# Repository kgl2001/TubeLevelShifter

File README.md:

# Tube Level Shifter for use with BBC Micro and Master 128 computers.

This project allows a Raspberry Pi to be connected to the Tube port on the BBC Micro and Master 128 computers. With the [PiTubeDirect](https://github.com/hoglet67/PiTubeDirect/wiki) software loaded onto the Pi, the following list of co-processors can be emulated:

```
 n   Processor - *FX 151,230,n
 0   65C02 (fast)
 1   65C02 (3MHz)
 2   65C102 (fast)
 3   65C102 (4MHz)
 4   Z80 (1.21)
 5   Z80 (2.00)
 6   Z80 (2.2c)
 7   Z80 (2.30)
 8   80186
 9   MC6809
11   PDP-11
12   ARM2
13   32016
14   Disable
15   ARM Native
16   LIB65C02 64K
17   LIB65C02 256K Turbo
18   65C816 (Dossy)
19   65C816 (ReCo)
20   OPC5LS
21   OPC6
22   OPC7
23   RISC-V
24 * 65C02 (JIT)
28   Ferranti F100-L
```

Most Pi models are compatible with PiTubeDirect. The smaller PiZero, PiZeroW or PiZero2W and level shifter can sit under a Beeb or Master.

The larger Pi1, Pi2, Pi3A/B & Pi4 models are also supported via a cable as they won't fit under the computer.

The latest PiTubeDirect software can be downloaded from the following site:

https://github.com/hoglet67/PiTubeDirect/releases

Some general notes:

* The source files are to be used with KiCAD v9.0.0 or later.
* The gerber files have been optimised for fabrication by JLCPCB. In particular, there is a 8mmx8mm silkscreen box on the rear of the PCB. This is to allow a 2D barcode, with unique serial number to be printed on the PCB.
* If you want the barcode to be added, then make sure to select this option in the 'Mark on PCB' field, and make sure to select 'Specify position' in the '2D Barcode Position' field, otherwise you will end up with a white 8mm x 8mm box printed on your PCB and a 8mm x 8mm barcode printed at a position of JLCPCBs choosing. Thrust me on this!
* If you don't want the barcode added, then remove the 8mm x 8mm box from the silkscreen layer and regenerate the gerbers. Otherwise you will end up with a white 8mm x 8mm box printed on your PCB.
* A combined CPL / BOM file is included in the gerber directory. Again, this is for use with JLCPCB, if you want to use their PCBA (PCB Assembly) to solder on all the SMD parts.
* You will need to source suitable 40 pin right angle and 40 pin straight through sockets, and solder these onto the PCB. The Raspberry Pi will connect to the 40 pin straight through socket and the level shifter will plug into the tube port via the 40 pin right angle socket.
* Be aware that it is possible to misalign the 40 pin right angle socket both vertically and horizontally when plugging it into the tube port so take care to ensure it is aligned correctly.
* The pins on the tube port connector may be tarnished if the header has not been used for many years. This can cause unreliable operation. This can usually be fixed with repeated removal and re-insertion of the level shifter into the header.
* Do not use a ribbon cable to connect the Raspberry Pi to the level shifter. Instead, the Raspberry Pi should be plugged directly into the level shifter.
* The level shifter can be plugged directly into the tube port in the well underneath the keyboard, or it can be attached to the tube port via a 40 way male / female ribbon cable.
* There is limited space in the well underneath the Master, so the the level shifter should initially be inserted at an angle and then straightened out as the level shifter is pushed home into the tube port.
* Due to the limited space underneath the Master, a compromise had to be made on the overall size of the level shifter board. Therefore, when fitting the level shifter into the Model B it may not be possible to push the level shifter fully into the tube port socket, otherwise the front face of the Pi will clash with part of the computer case.
* An optional power header can be attached to the level shifter. This header can then be used to power the Pi1MHz level shifter and assocaited Raspberry Pi, if attached to the 1MHz bus. The 5v supply is protected by a 500mA Poylfuse.
* If the level shifter is connected to the tube port via a ribbon cable then the simplest way to power the level shifter and Raspberry Pi is via a standard Raspberry Pi power supply connected to the Raspberry Pi. This will also power the level shifter. In this case, jumper J1 should be removed to prevent the Raspberry Pi supply from powering the main computer.

## Developer

The 1MHz level shifter board is developed and maintained by Ken Lowe.
    
## Hardware License (Creative Commons BY-SA 4.0)

Please see the following link for details: https://creativecommons.org/licenses/by-sa/4.0/

You are free to:

Share - copy and redistribute the material in any medium or format
Adapt - remix, transform, and build upon the material
for any purpose, even commercially.

This license is acceptable for Free Cultural Works.

The licensor cannot revoke these freedoms as long as you follow the license terms.

Under the following terms:

Attribution - You must give appropriate credit, provide a link to the license, and indicate if changes were made. You may do so in any reasonable manner, but not in any way that suggests the licensor endorses you or your use.

ShareAlike - If you remix, transform, or build upon the material, you must distribute your contributions under the same license as the original.

No additional restrictions - You may not apply legal terms or technological measures that legally restrict others from doing anything the license permits.

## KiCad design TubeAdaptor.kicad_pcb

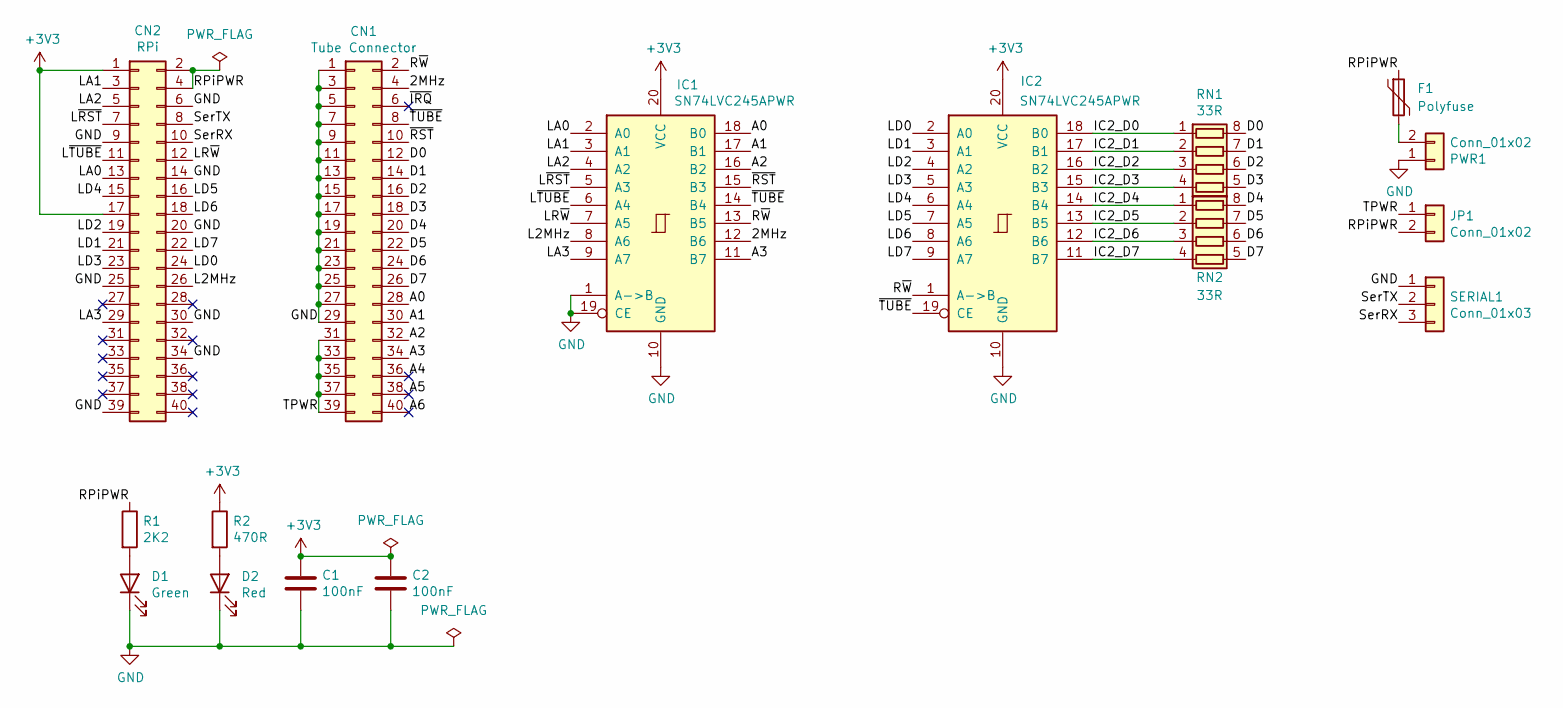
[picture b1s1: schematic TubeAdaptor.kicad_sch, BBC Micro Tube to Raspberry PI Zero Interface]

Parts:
C1, C2: 100nF; C_0402_1005Metric; JLC Part Number C1525
CN1: Tube Connector; PinSocket_2x20_P2.54mm_Horizontal_Reverse
CN2: RPi; PinSocket_2x20_P2.54mm_Vertical
D1: Green; LED_0603_1608Metric; JLC Part Number C72043
D2: Red; LED_0603_1608Metric; JLC Part Number C2286
F1: Polyfuse; Fuse_0603_1608Metric; JLC Part Number C883095
IC1, IC2: SN74LVC245APWR; TSSOP-20_4.4x6.5mm_P0.65mm; JLC Part Number C7848
JP1: Conn_01x02; PinHeader_1x02_P2.54mm_Vertical
PWR1: Conn_01x02; PinHeader_1x02_P2.54mm_Horizontal
R1: 2K2; R_0402_1005Metric; JLC Part Number C25879
R2: 470R; R_0402_1005Metric; JLC Part NumberJLC Part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 C25117
RN1, RN2: 33R; R_Array_Concave_4x0402; JLC Part Number C25501
SERIAL1: Conn_01x03; PinHeader_1x03_P2.54mm_Horizontal

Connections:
+3V3: C1.1, C2.1, CN2.1, CN2.17, IC1.20 (VCC), IC2.20 (VCC), R2.1
/2MHz: CN1.4, IC1.12 (B6)
/A0: CN1.28, IC1.18 (B0)
/A1: CN1.30, IC1.17 (B1)
/A2: CN1.32, IC1.16 (B2)
/A3: CN1.34, IC1.11 (B7)
/A4: CN1.36
/A5: CN1.38
/A6: CN1.40
/D0: CN1.12, RN1.8 (R1.2)
/D1: CN1.14, RN1.7 (R2.2)
/D2: CN1.16, RN1.6 (R3.2)
/D3: CN1.18, RN1.5 (R4.2)
/D4: CN1.20, RN2.8 (R1.2)
/D5: CN1.22, RN2.7 (R2.2)
/D6: CN1.24, RN2.6 (R3.2)
/D7: CN1.26, RN2.5 (R4.2)
/IC2_D0: IC2.18 (B0), RN1.1 (R1.1)
/IC2_D1: IC2.17 (B1), RN1.2 (R2.1)
/IC2_D2: IC2.16 (B2), RN1.3 (R3.1)
/IC2_D3: IC2.15 (B3), RN1.4 (R4.1)
/IC2_D4: IC2.14 (B4), RN2.1 (R1.1)
/IC2_D5: IC2.13 (B5), RN2.2 (R2.1)
/IC2_D6: IC2.12 (B6), RN2.3 (R3.1)
/IC2_D7: IC2.11 (B7), RN2.4 (R4.1)
/L2MHz: CN2.26, IC1.8 (A6)
/LA0: CN2.13, IC1.2 (A0)
/LA1: CN2.3, IC1.3 (A1)
/LA2: CN2.5, IC1.4 (A2)
/LA3: CN2.29, IC1.9 (A7)
/LD0: CN2.24, IC2.2 (A0)
/LD1: CN2.21, IC2.3 (A1)
/LD2: CN2.19, IC2.4 (A2)
/LD3: CN2.23, IC2.5 (A3)
/LD4: CN2.15, IC2.6 (A4)
/LD5: CN2.16, IC2.7 (A5)
/LD6: CN2.18, IC2.8 (A6)
/LD7: CN2.22, IC2.9 (A7)
/LR~W: CN2.12, IC1.7 (A5)
/L~RST: CN2.7, IC1.5 (A3)
/L~TUBE: CN2.11, IC1.6 (A4)
/RPiPWR: CN2.2, CN2.4, F1.1, JP1.2, R1.1
/R~W: CN1.2, IC1.13 (B5), IC2.1 (A->B)
/SerRX: CN2.10, SERIAL1.3
/SerTX: CN2.8, SERIAL1.2
/TPWR: CN1.31, CN1.33, CN1.35, CN1.37, CN1.39, JP1.1
/~IRQ: CN1.6
/~RST: CN1.10, IC1.15 (B3)
/~TUBE: CN1.8, IC1.14 (B4), IC2.19 (CE)
GND: C1.2, C2.2, CN1.1, CN1.3, CN1.5, CN1.7, CN1.9, CN1.11, CN1.13, CN1.15, CN1.17, CN1.19, CN1.21, CN1.23, CN1.25, CN1.27, CN1.29, CN2.6, CN2.9, CN2.14, CN2.20, CN2.25, CN2.30, CN2.34, CN2.39, D1.1 (K), D2.1 (K), IC1.1 (A->B), IC1.10 (GND), IC1.19 (CE), IC2.10 (GND), PWR1.1, SERIAL1.1
unnamed: D1.2 (A), R1.2
unnamed: D2.2 (A), R2.2
unnamed: F1.2, PWR1.2

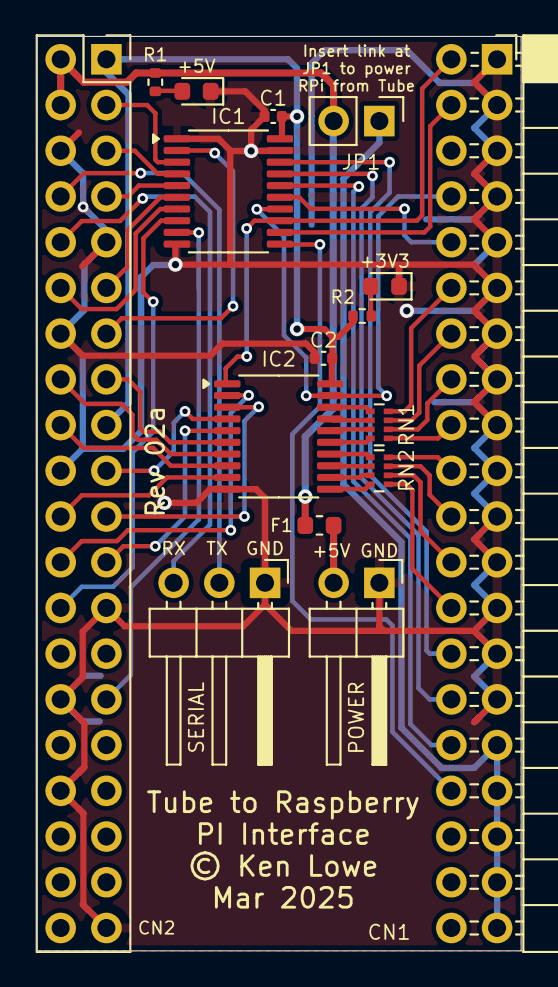
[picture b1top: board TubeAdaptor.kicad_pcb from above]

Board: 2 copper layers, 26.9 x 50.8 mm, 16 parts (0 on the bottom side), 49 nets.

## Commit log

2025-03-31 First public release
2025-04-01 Add pdf copy of schematic

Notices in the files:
TubeAdaptor.kicad_pcb:
© Ken Lowe
